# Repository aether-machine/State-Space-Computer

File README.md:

This repository began it's life as the Oscilloplasm module which existed for a brief time in the Wiard 300 Series format, and has now expanded into a complete and separate take on the audio synthesis paradigm based on continuous computing techniques that occur in the physical and non-physical domains. Here, we present both a general method to solve computing problems using electronic means, and ready made solutions to build and install yourself. The licensing is strictly for non-commercial use only, e.g. education, DIY.

The place to begin is the representation of physical phenomena as periodic information, starting in two dimensions as sound waves and following through into three dimensional particles as persistant standing wave patterns that make up our physical universe. This representation can be done in maths using differential equations, from simple linear ordinary differential equations (ODEs) that describe electron shell configurations, into complex non-linear partial differential equations (PDEs) that can describe motion in a body of water, likely with multiple flow velocities and different viscosities. At the most extreme form, a single equation might be able to describe the entire universe, for example reaction-diffusion equations can give rise to cell like growth.

The primitive in analog computing is the state variable, which appears in both the harmonic oscillator (sine wave) and the multimode filter. Mathematically:

$$
\frac{d^2x}{dt^2} + 2\gamma \frac{dx}{dt} + \omega^2 x = F(t)
$$

Where ω = 2πf is the angular frequency of the sine wave and the first derivative x' controls damping or growth. To solve in analog form, the second differential x'' (with respect to time) is passed through two voltage controlled integrators, each comprised of a variable transconductance stage, an opamp and a capacitor as a memory cell, with the inversion of the x output connected to the input to solve. This is the general form of solving ODEs using electronic means, to re-arrange in terms of the lowest order derivative, assume that it exists, and then solve by parts using cascaded integrator stages, the final integrator stage then represents the solution and this is used as the input to complete the cycle.

The harmonic oscillator circuit here is unique to the system, a self stablizing sine wave based around a trig identity for instant in the loop gain correction:

$$
sin^2 + cos^2 - 1 = 0
$$

Using two Gilbert Cell mulitpliers and a zener diode stabilized DC reference, this generates a real time error value which can be used to modulate the oscillator loop gain and maintain long term amplitude stability, as well as two second harmonic outputs for the sine and cosine portions of the waveform. The complete equation with stabilization is:

$$
\frac{d^2 x}{dt^2} + 2k\epsilon \frac{dx}{dt} + \left(\omega^2 + k^2\epsilon^2\right)x = 0
$$

Output oscillator is a variable harmonic wavetable that solves Legendre's Ordinary Differential Equation in real time:

$$
(1 - t^2) \frac{d^2x}{dt^2} - 2t \omega \frac{dx}{dt} + (\omega^2 - l(l+1))x = 0
$$

Where L represents the azimuthal quantum number, thus generating polynomial functions in a completely novel (and sometimes frustrating) way.

The stabilization technique in this oscillator is also state of the art, although there is a compromise between harmonic distortion and ampltiude distortion. Ampltitude distortion as the RMS to DC converter gets stuck in a modulation loop is probably the more destructive force here for audio work. It can be mitigated by avoiding rapid changes in oscillator frequency, perhaps by using a slew limiter on your seqeuncer.

Output oscillator uses four quadrant multipliers and is designed for through zero behaviour.

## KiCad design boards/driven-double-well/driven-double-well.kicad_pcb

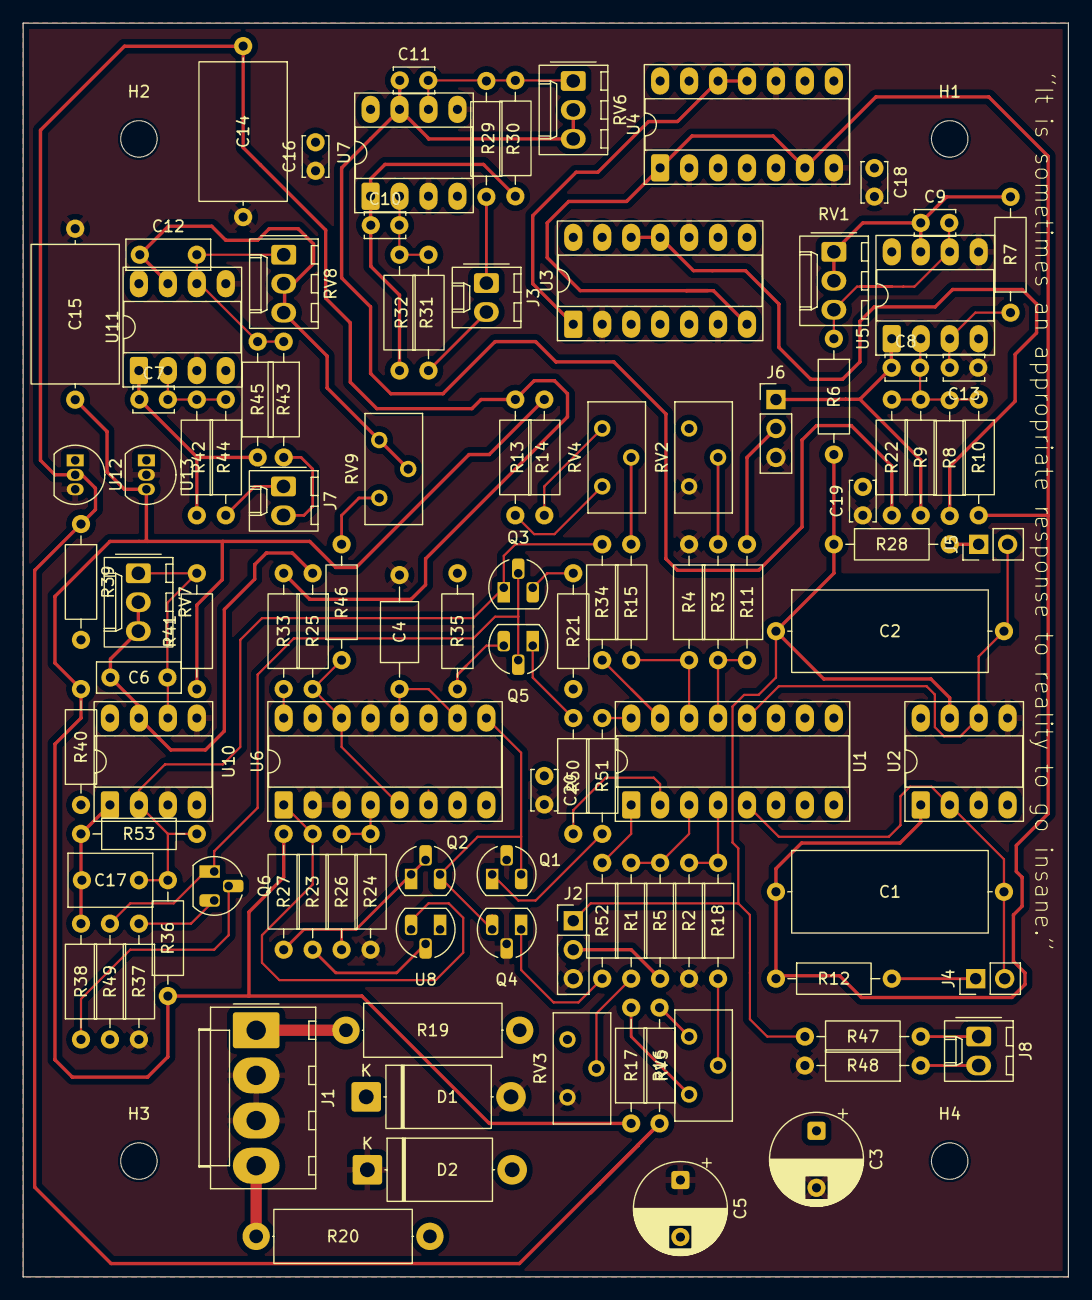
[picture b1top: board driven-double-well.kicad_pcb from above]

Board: 4 copper layers, 91.7 x 110.0 mm, 114 parts (0 on the bottom side), 73 nets.

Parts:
C1, C2: C; C_Axial_L17.0mm_D7.0mm_P20.00mm_Horizontal
C3, C5: C_Polarized; CP_Radial_D8.0mm_P5.00mm
C4: C; C_Axial_L5.1mm_D3.1mm_P10.00mm_Horizontal
C6, C12: C; C_Rect_L7.2mm_W2.5mm_P5.00mm_FKS2_FKP2_MKS2_MKP2
C7, C8, C9, C10, C11, C13, C16, C18, C19, C20: C; C_Disc_D3.4mm_W2.1mm_P2.50mm
C14, C15: C; C_Axial_L12.0mm_D7.5mm_P15.00mm_Horizontal
C17: C; C_Rect_L7.2mm_W4.5mm_P5.00mm_FKS2_FKP2_MKS2_MKP2
D1, D2: 1N630xA; D_DO-201AE_P12.70mm_Horizontal
H1, H2, H3, H4: MountingHole; MountingHole_3.2mm_M3
J1: Conn_01x04; Molex_KK-396_A-41791-0004_1x04_P3.96mm_Vertical
J2, J6: Conn_01x03; PinHeader_1x03_P2.54mm_Vertical
J3, J7, J8: Conn_01x02; Molex_KK-254_AE-6410-02A_1x02_P2.54mm_Vertical
J4, J5: Conn_01x02; PinHeader_1x02_P2.54mm_Vertical
Q1, Q2, Q3, Q4, Q5: BC560; TO-92_HandSolder
Q6: BC550; TO-92_HandSolder
R1, R2, R3, R4, R12, R23, R24, R25, R28, R33, R36, R37, R46, R51, R52: 1k; R_Axial_DIN0207_L6.3mm_D2.5mm_P10.16mm_Horizontal
R5, R11: R; R_Axial_DIN0207_L6.3mm_D2.5mm_P10.16mm_Horizontal
R6, R8, R9, R10, R13, R14, R16, R17, R22, R27, R29, R30, R31, R32, R38, R41, R42, R43, R44, R45: 10k; R_Axial_DIN0207_L6.3mm_D2.5mm_P10.16mm_Horizontal
R7: 2.5k; R_Axial_DIN0207_L6.3mm_D2.5mm_P10.16mm_Horizontal
R15, R18: 200k; R_Axial_DIN0207_L6.3mm_D2.5mm_P10.16mm_Horizontal
R19, R20: R; R_Axial_DIN0414_L11.9mm_D4.5mm_P15.24mm_Horizontal
R21, R34, R35, R47, R48, R50: 100; R_Axial_DIN0207_L6.3mm_D2.5mm_P10.16mm_Horizontal
R26: 5k; R_Axial_DIN0207_L6.3mm_D2.5mm_P10.16mm_Horizontal
R39, R40: R_Axial_DIN0207_L6.3mm_D2.5mm_P10.16mm_Horizontal
R49: 4.7k; R_Axial_DIN0207_L6.3mm_D2.5mm_P10.16mm_Horizontal
R53: 1meg; R_Axial_DIN0207_L6.3mm_D2.5mm_P10.16mm_Horizontal
RV1, RV6, RV7, RV8: R_Potentiometer; Molex_KK-254_AE-6410-03A_1x03_P2.54mm_Vertical
RV2, RV3, RV4, RV5, RV9: R_Potentiometer; Potentiometer_Bourns_3296Y_Vertical
U1, U6: LM13700; DIP-16_W7.62mm_Socket_LongPads
U2, U5, U7, U10, U11: TL072; DIP-8_W7.62mm_Socket_LongPads
U3, U4: MPY634KP; DIP-14_W7.62mm_Socket_LongPads
U8: LM334Z; TO-92_HandSolder
U12, U13: LM4040LP-10; TO-92_Inline

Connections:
+15V: C3.1, C16.2, C19.2, D1.1 (A1), R19.1, R21.1, R35.1, R39.2, R49.2, U1.11 (V+), U2.8 (V+), U3.14 (+V_{S}), U4.14 (+V_{S}), U5.8 (V+), U6.11 (V+), U7.8 (V+), U8.1, U10.8 (V+), U11.8 (V+)
-15V: C5.2, C18.1, C20.1, D2.2 (A2), R20.1, R40.1, U1.6 (V-), U2.4 (V-), U3.8 (-V_{S}), U4.8 (-V_{S}), U5.4 (V-), U6.6 (V-), U7.4 (V-), U10.4 (V-), U11.4 (V-)
/VREF_N10: C15.2, R13.2, R17.1, R27.1, R36.1, R40.2, R41.1, U13.3 (A)
/VREF_P10: C14.1, R14.1, R16.2, R33.1, R39.1, U12.2 (K)
GND: C3.2, C4.2, C5.1, C13.1, C14.2, C15.1, C16.1, C18.2, C19.1, C20.2, D1.2 (A2), D2.1 (A1), J1.2, J1.3, J2.3, J6.3, Q1.2 (B), Q4.2 (B), R2.2, R4.2, R24.2, R37.2, R48.2, RV2.3, RV3.3, U2.3 (+), U2.5 (+), U3.2 (X_{2}), U3.6 (Y_{1}), U3.10 (Z_{2}), U4.2 (X_{2}), U4.7 (Y_{2}), U4.10 (Z_{2}), U5.5 (+), U6.2 (DIODE_BIAS), U6.3 (+), U6.13 (-), U7.3 (+), U7.5 (+), U10.3 (+), U10.5 (+), U11.3 (+), U11.5 (+), U12.3 (A), U13.2 (K)
unnamed: C4.1, U6.10, U6.12
unnamed: C6.1, R25.1, RV7.2, RV7.3, U10.7
unnamed: C7.1, R44.2, R45.1, U11.1
unnamed: C9.1, R7.2, RV1.1, RV1.2, U5.7
unnamed: C10.1, R29.1, R31.2, U7.1
unnamed: C11.1, R22.1, RV6.2, RV6.3, U7.7
unnamed: C12.1, RV8.2, RV8.3, RV9.1, RV9.2, U11.7
unnamed: C17.1, R38.2, R53.1, U10.1
unnamed: J1.1, R19.2
unnamed: J1.4, R20.2
unnamed: C2.1, J2.1, R6.2, R28.1, R47.2, U2.7
unnamed: J2.2, R5.2
unnamed: J3.1, R30.2
unnamed: J3.2, R32.1
unnamed: J4.1, R12.2
unnamed: C1.2, J4.2, U1.5, U2.2 (-)
unnamed: J5.1, R28.2
unnamed: C2.2, J5.2, U1.12, U2.6 (-)
unnamed: C8.1, J6.1, R9.1, U5.1
unnamed: J6.2, R11.2
unnamed: J7.1, R42.1
unnamed: J7.2, R43.2
unnamed: J8.1, R47.1
unnamed: J8.2, R48.1
unnamed: Q1.1 (C), R51.2
unnamed: Q1.3 (E), Q2.3 (E), Q4.3 (E), U6.9
unnamed: Q2.1 (C), Q2.2 (B), R26.1, R27.2
unnamed: Q3.2 (B), Q5.2 (B), Q6.1 (C), R49.1
unnamed: C17.2, Q3.1 (C), R34.1, R36.2, R53.2, U10.2 (-)
unnamed: Q3.3 (E), R21.2
unnamed: Q4.1 (C), R52.2
unnamed: Q5.1 (C), R50.1
unnamed: Q5.3 (E), R35.2
unnamed: Q6.2 (B), R38.1
unnamed: Q6.3 (E), R37.1
unnamed: R1.2, RV3.2
unnamed: R3.2, RV2.2
unnamed: R13.1, RV4.1
unnamed: R14.2, RV4.3
unnamed: R15.2, RV4.2
unnamed: R16.1, RV5.1
unnamed: R17.2, RV5.3
unnamed: R18.2, RV5.2
unnamed: R23.1, U8.2
unnamed: R23.2, U6.1, U8.3
unnamed: R33.2, U6.16
unnamed: R46.2, RV9.3
unnamed: R51.1, U1.16
unnamed: R52.1, U1.1
unnamed: R4.1, R15.1, U1.14 (+)
unnamed: R3.1, R11.1, U1.13 (-)
unnamed: R34.2, U1.15 (DIODE_BIAS)
unnamed: R1.1, R5.1, U1.3 (+)
unnamed: R2.1, R18.1, U1.4 (-)
unnamed: R50.2, U1.2 (DIODE_BIAS)
unnamed: R8.1, U3.11 (Z_{1}), U3.12 (V_{O})
unnamed: U3.1 (X_{1}), U4.11 (Z_{1}), U4.12 (V_{O})
unnamed: C1.1, R10.2, R12.1, U2.1, U3.7 (Y_{2}), U4.1 (X_{1}), U4.6 (Y_{1})
unnamed: C13.2, R7.1, U5.3 (+)
unnamed: C8.2, R8.2, R9.2, R10.1, R22.2, U5.2 (-)
unnamed: C9.2, R6.1, RV1.3, U5.6 (-)
unnamed: R25.2, R46.1, U6.5, U6.14 (+)
unnamed: R24.1, R26.2, U6.4 (-)
unnamed: C10.2, R31.1, R32.2, U7.2 (-)
unnamed: C11.2, R29.2, R30.1, RV6.1, U7.6 (-)
unnamed: C6.2, R41.2, RV7.1, U10.6 (-)
unnamed: C7.2, R42.2, R44.1, U11.2 (-)
unnamed: C12.2, R43.1, R45.2, RV8.1, U11.6 (-)

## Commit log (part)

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2026-05-14 Create driven-double-well
2026-05-14 Update driven-double-well
